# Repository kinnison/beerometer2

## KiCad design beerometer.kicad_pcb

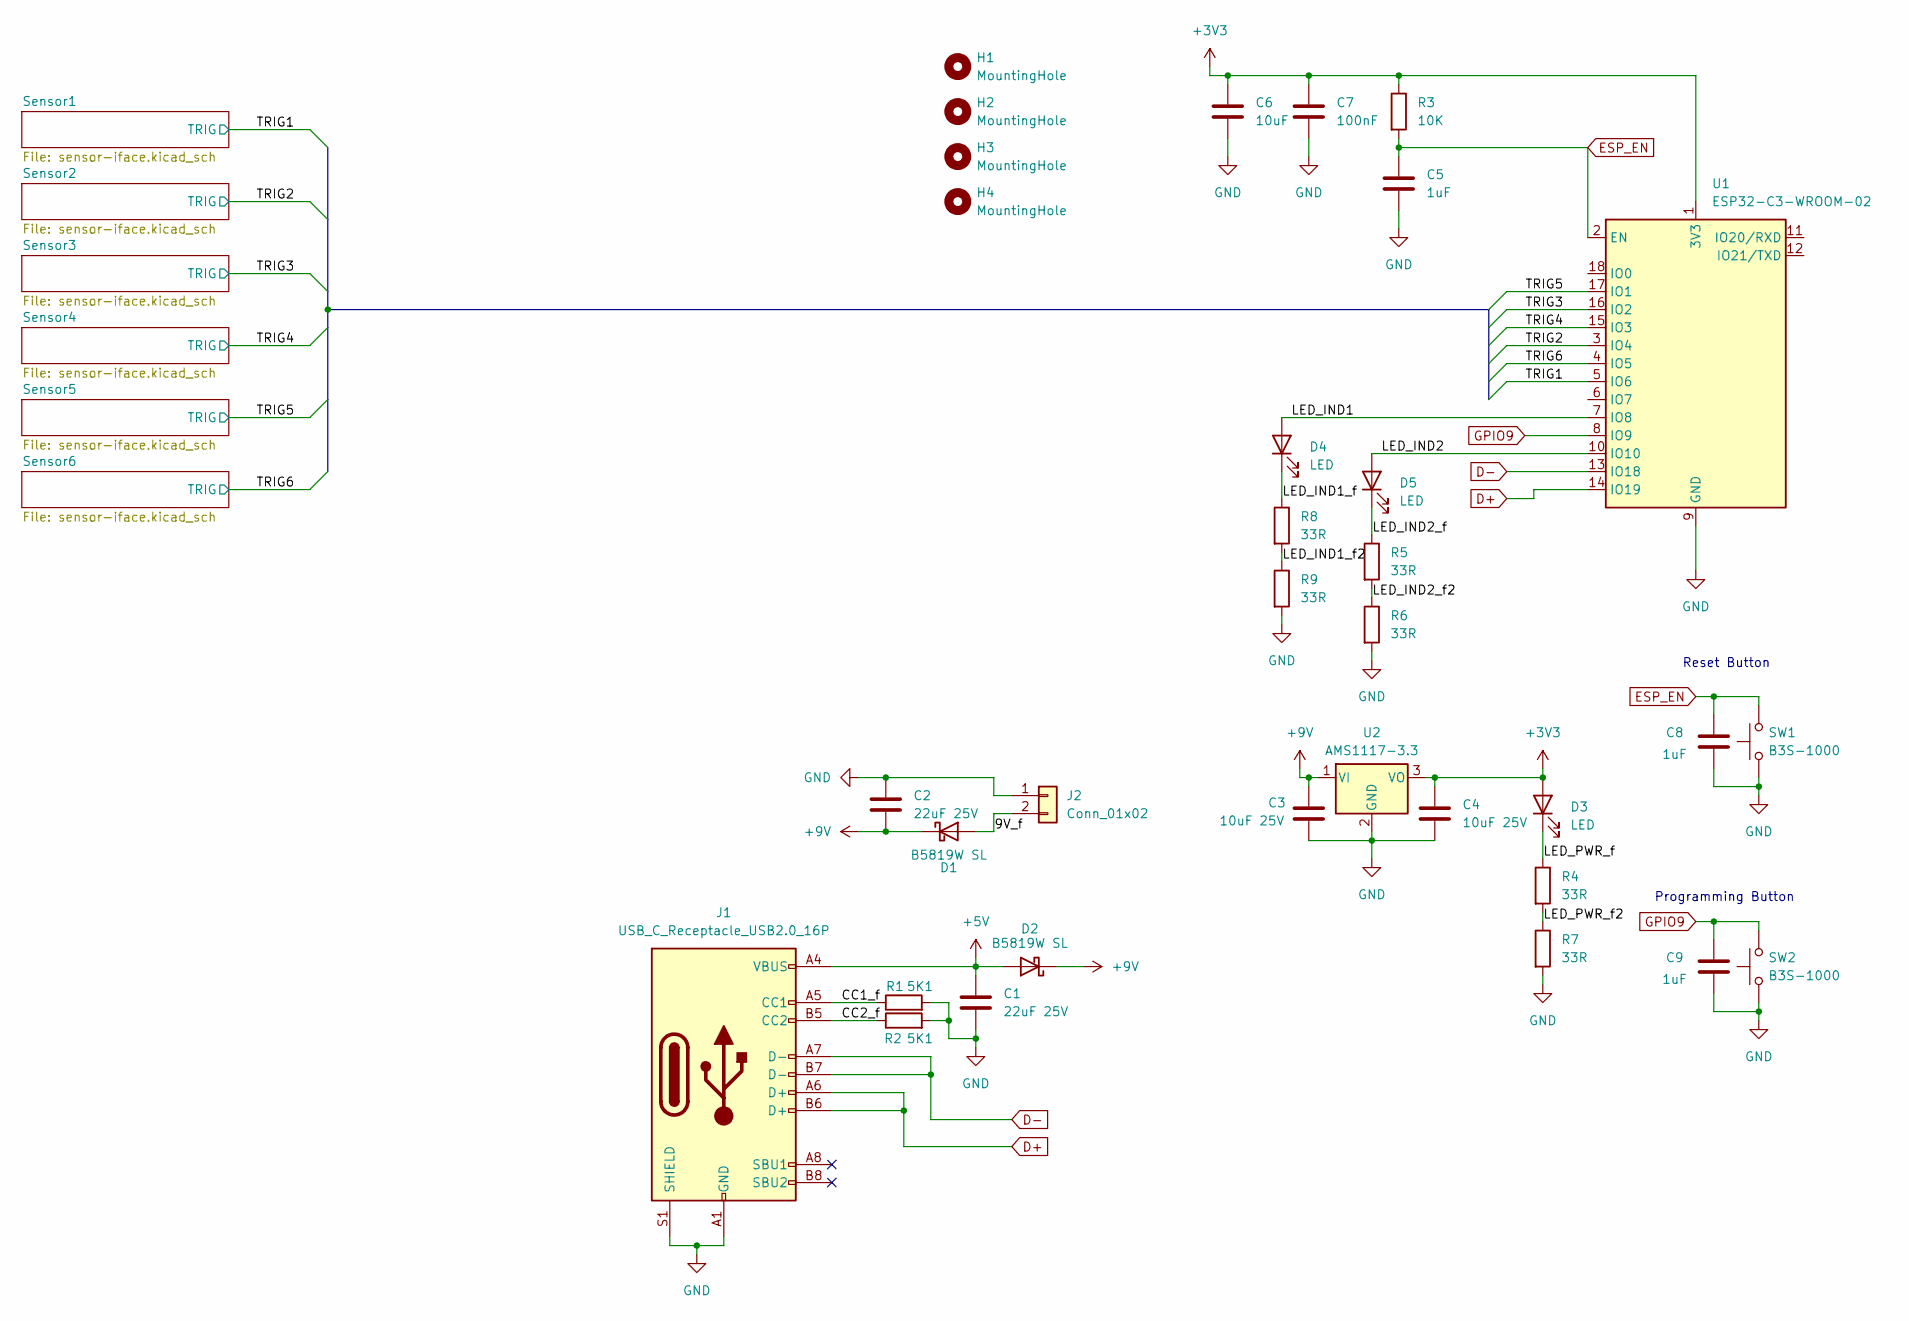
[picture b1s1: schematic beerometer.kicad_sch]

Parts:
C1, C2: 22uF 25V; C_1206_3216Metric; JLCPCB Part # C12891
C3, C4: 10uF 25V; C_0603_1608Metric; JLCPCB Part # C96446
C5, C8, C9: 1uF; C_0603_1608Metric
C6: 10uF; C_0603_1608Metric; JLCPCB Part # C96446
C7: 100nF; C_0603_1608Metric; JLCPCB Part # C14663
D1, D2: B5819W SL; D_SOD-123; JLCPCB Part # C8598
D3, D4, D5: LED; LED_0603_1608Metric; JLCPCB Part # C2286
H1, H2, H3, H4: MountingHole; MountingHole_2.5mm
J1: USB_C_Receptacle_USB2.0_16P; USB_C_Receptacle_XKB_U262-16XN-4BVC11; JLCPCB Part # C319148
J2: Conn_01x02; PinHeader_1x02_P2.54mm_Vertical; JLCPCB Part # C492401
R1, R2: 5K1; R_0402_1005Metric
R3: 10K; R_0402_1005Metric; JLCPCB Part # C25744
R4, R5, R6, R7, R8, R9: 33R; R_0402_1005Metric; JLCPCB Part # C25105
SW1, SW2: B3S-1000; SW_SPST_B3S-1000
U1: ESP32-C3-WROOM-02; JLCPCB Part # C2934560
U2: AMS1117-3.3; SOT-223-3_TabPin2; JLCPCB Part # C6186

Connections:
+3V3: C4.1, C6.1, C7.1, D3.2 (A), R3.1, U1.1 (3V3), U2.3 (VO)
+5V: C1.1, D2.2 (A), J1.A4 (VBUS), J1.A9 (VBUS), J1.B4 (VBUS), J1.B9 (VBUS)
+9V: C2.2, C3.1, D1.1 (K), D2.1 (K), U2.1 (VI); also elsewhere on the board
/9V_f: D1.2 (A), J2.2
/CC1_f: J1.A5 (CC1), R1.1
/CC2_f: J1.B5 (CC2), R2.1
/LED_IND1: D4.2 (A), U1.7 (IO8)
/LED_IND1_f: D4.1 (K), R8.1
/LED_IND1_f2: R8.2, R9.1
/LED_IND2: D5.2 (A), U1.10 (IO10)
/LED_IND2_f: D5.1 (K), R5.1
/LED_IND2_f2: R5.2, R6.1
/LED_PWR_f: D3.1 (K), R4.1
/LED_PWR_f2: R4.2, R7.1
/TRIG1: U1.5 (IO6); also elsewhere on the board
/TRIG2: U1.3 (IO4); also elsewhere on the board
/TRIG3: U1.16 (IO2); also elsewhere on the board
/TRIG4: U1.15 (IO3); also elsewhere on the board
/TRIG5: U1.17 (IO1); also elsewhere on the board
/TRIG6: U1.4 (IO5); also elsewhere on the board
D+: J1.A6 (D+), J1.B6 (D+), U1.14 (IO19)
D-: J1.A7 (D-), J1.B7 (D-), U1.13 (IO18)
ESP_EN: C5.1, C8.2, R3.2, SW1.2, U1.2 (EN)
GND: C1.2, C2.1, C3.2, C4.2, C5.2, C6.2, C7.2, C8.1, C9.1, J1.A1 (GND), J1.A12 (GND), J1.B1 (GND), J1.B12 (GND), J1.S1 (SHIELD), J2.1, R1.2, R2.2, R6.2, R7.2, R9.2, SW1.1, SW2.1, U1.9 (GND), U1.19 (GND), U2.2 (GND); also elsewhere on the board
GPIO9: C9.2, SW2.2, U1.8 (IO9)

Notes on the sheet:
Reset Button
Programming Button

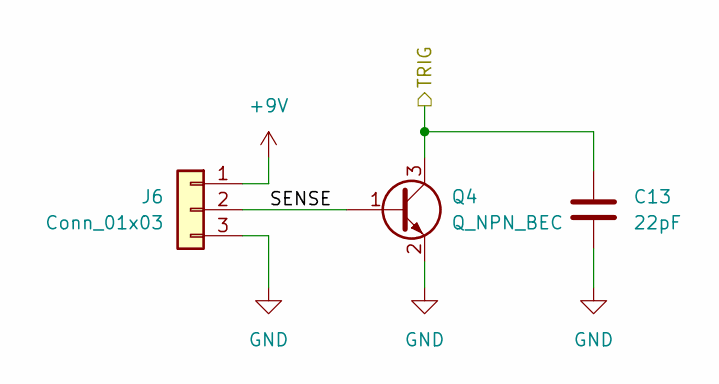
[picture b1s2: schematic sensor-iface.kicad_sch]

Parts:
C13: 22pF; C_0603_1608Metric; JLCPCB Part # C1653
J6: Conn_01x03; PinHeader_1x03_P2.54mm_Vertical; JLCPCB Part # C2937625
Q4: Q_NPN_BEC; SOT-23; JLCPCB Part # C20526

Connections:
+9V: J6.1; also elsewhere on the board
/Sensor4/SENSE: J6.2, Q4.1 (B)
/TRIG4: C13.1, Q4.3 (C); also elsewhere on the board
GND: C13.2, J6.3, Q4.2 (E); also elsewhere on the board

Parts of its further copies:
C10, C11, C12, C14, C15: 22pF; C_0603_1608Metric; JLCPCB Part # C1653
J3, J4, J5, J7, J8: Conn_01x03; PinHeader_1x03_P2.54mm_Vertical; JLCPCB Part # C2937625
Q1, Q2, Q3, Q5, Q6: Q_NPN_BEC; SOT-23; JLCPCB Part # C20526

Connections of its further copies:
+9V: J3.1, J4.1, J5.1, J7.1, J8.1; also elsewhere on the board
/Sensor1/SENSE: J3.2, Q1.1 (B)
/Sensor2/SENSE: J4.2, Q2.1 (B)
/Sensor3/SENSE: J5.2, Q3.1 (B)
/Sensor5/SENSE: J7.2, Q5.1 (B)
/Sensor6/SENSE: J8.2, Q6.1 (B)
/TRIG1: C10.1, Q1.3 (C); also elsewhere on the board
/TRIG2: C11.1, Q2.3 (C); also elsewhere on the board
/TRIG3: C12.1, Q3.3 (C); also elsewhere on the board
/TRIG5: C14.1, Q5.3 (C); also elsewhere on the board
/TRIG6: C15.1, Q6.3 (C); also elsewhere on the board
GND: C10.2, C11.2, C12.2, C14.2, C15.2, J3.3, J4.3, J5.3, J7.3, J8.3, Q1.2 (E), Q2.2 (E), Q3.2 (E), Q5.2 (E), Q6.2 (E); also elsewhere on the board

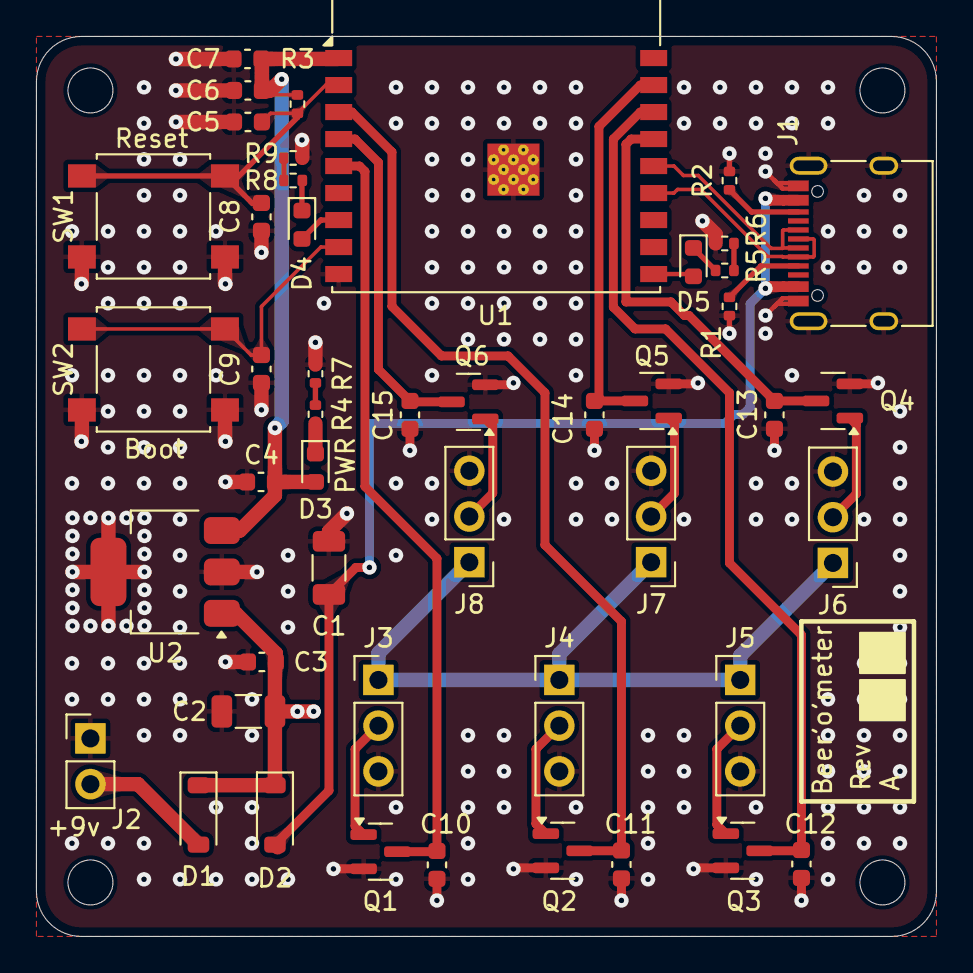
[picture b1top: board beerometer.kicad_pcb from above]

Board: 2 copper layers, 50.0 x 50.0 mm, 51 parts (0 on the bottom side), 31 nets.

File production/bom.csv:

Designator,Footprint,Quantity,Value,LCSC Part #
"C1, C2",1206,2,22uF 25V,C12891
"C10, C11, C12, C13, C14, C15",0603,6,22pF,C1653
"C3, C4",0603,2,10uF 25V,C96446
"C5, C8, C9",0603,3,1uF,
C6,0603,1,10uF,C96446
C7,0603,1,100nF,C14663
"D1, D2",D_SOD-123,2,B5819W SL,C8598
"D3, D4, D5",0603,3,LED,C2286
J1,USB_C_Receptacle_XKB_U262-16XN-4BVC11,1,USB_C_Receptacle_USB2.0_16P,C319148
"Q1, Q2, Q3, Q4, Q5, Q6",SOT-23,6,Q_NPN_BEC,C20526
"R1, R2",0402,2,5K1,
R3,0402,1,10K,C25744
"R4, R5, R6, R7, R8, R9",0402,6,33R,C25105
"SW1, SW2",SW_SPST_B3S-1000,2,B3S-1000,
U1,ESP32-C3-WROOM-02,1,ESP32-C3-WROOM-02,C2934560
U2,SOT-223-3_TabPin2,1,AMS1117-3.3,C6186

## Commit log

2024-12-28 chore: Initial commit
